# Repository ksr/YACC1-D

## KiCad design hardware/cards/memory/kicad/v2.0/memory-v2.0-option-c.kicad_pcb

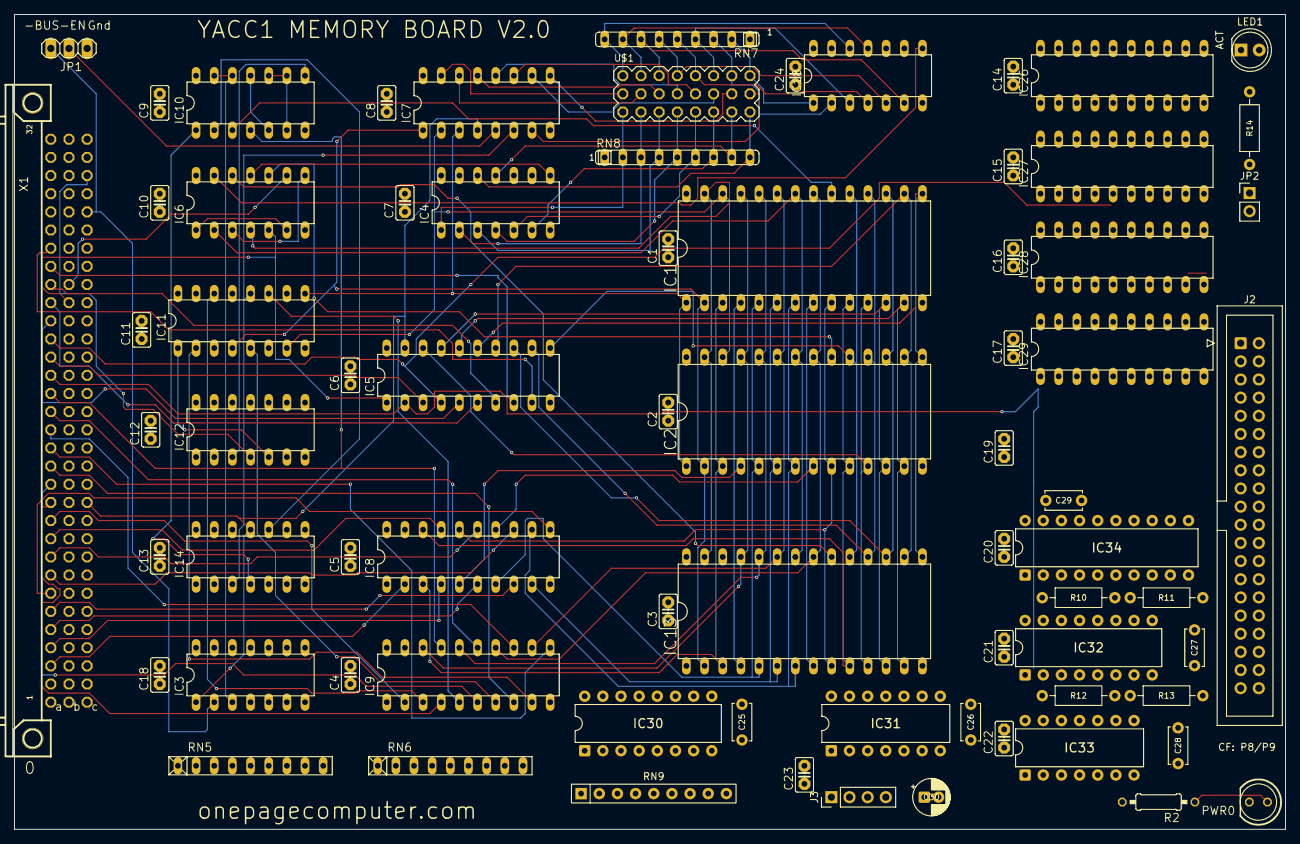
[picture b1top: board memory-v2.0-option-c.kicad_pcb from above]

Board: 4 copper layers, 177.8 x 114.0 mm, 73 parts (0 on the bottom side), 147 nets.

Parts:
C1, C2, C3, C4, C5, C6, C7, C8, C9, C10, C11, C12, C13, C14, C15, C16, C17, C18, C19, C20, C21, C22, C23, C24: C025-025X050
C25, C26, C27, C28, C29: 100n; C_Disc_D5.0mm_W2.5mm_P5.00mm
C30: 10u; CP_Radial_D5.0mm_P2.00mm
IC1, IC2, IC13: DIL28-6
IC3: 74LS32N; DIL14
IC4, IC18: 74ALS30N; DIL14
IC5: 74LS245N; DIL20
IC6, IC14: 74LS04N; DIL14
IC7: 74LS138N; DIL16
IC8, IC9: 74LS244N; DIL20
IC10: 74ALS00N; DIL14
IC11: 74LS157N; DIL16
IC12: 74LS74N; DIL14
IC26, IC27, IC28, IC29: 74LS374N; DIL20
IC30: 74LS138; DIP-16_W7.62mm
IC31: 74LS32; DIP-14_W7.62mm
IC32: 74LS175; DIP-16_W7.62mm
IC33: 74LS08; DIP-14_W7.62mm
IC34: 74LS245; DIP-20_W7.62mm
J2: IDE 40; IDC-Header_2x20_P2.54mm_Vertical
J3: POWER; PinHeader_1x04_P2.54mm_Vertical
JP1: 1X03
JP2: PIN20 5V; PinHeader_1x02_P2.54mm_Vertical
LED1: ACT yellow; LED_D5.0mm
PWR0: LED5MM
R2: 330; 0207_10
R10, R11, R12, R13: 10k; R_Axial_DIN0207_L6.3mm_D2.5mm_P10.16mm_Horizontal
R14: 1k; R_Axial_DIN0207_L6.3mm_D2.5mm_P10.16mm_Horizontal
RN5, RN6: RN-9
RN7, RN8: SIL9
RN9: 10k x8; R_Array_SIP9
U$1: PIN_3X8
X1: FABC96R

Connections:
-BUS-EN: IC3.2, JP1.1, X1.C28
-HI-RAM: IC2.20, IC6.10
-IO-RD: IC31.5, X1.B25
-IO-WR: IC31.2, IC31.10, X1.B26
-MEM-RD: IC5.1, IC6.5, X1.B23
-MEM-WR: IC6.9, X1.B24
-RESET: IC12.4, IC32.1, IC33.4, X1.C30
-ROM-CS: IC6.12, IC13.20
-TMP-REG-LD0: IC14.1, X1.B28
-TMP-REG-LD1: IC14.13, X1.B30
-TMP-REG-RD0: IC26.1, IC27.1, X1.B27
-TMP-REG-RD1: IC28.1, IC29.1, X1.B29
-VMA: IC3.1, IC5.19, IC7.4, IC14.11, X1.C12
/Sheet 3/-LO-RAM: IC1.20, IC10.3
/Sheet 7/-CFOE: IC33.3, IC33.9, IC33.10, IC34.19
/Sheet 7/-CFRESET: IC33.6, J2.1
/Sheet 7/-DASP: J2.39, R12.2
/Sheet 7/-DMACK: J2.29, R13.2
/Sheet 7/-IOR: IC31.6, IC33.1, IC34.1, J2.25
/Sheet 7/-IOW: IC31.8, IC33.2, J2.23
/Sheet 7/-P8SEL: IC30.15, IC31.1
/Sheet 7/-P9SEL: IC30.14, IC31.4, IC31.9
/Sheet 7/-PDIAG: J2.34, R11.2
/Sheet 7/-SRST: IC32.14, IC33.5
/Sheet 7/ACTK: IC33.8, LED1.1
/Sheet 7/CFD0: IC34.18, J2.17, RN9.2
/Sheet 7/CFD1: IC34.17, J2.15, RN9.3
/Sheet 7/CFD2: IC34.16, J2.13, RN9.4
/Sheet 7/CFD3: IC34.15, J2.11, RN9.5
/Sheet 7/CFD4: IC34.14, J2.9, RN9.6
/Sheet 7/CFD5: IC34.13, J2.7, RN9.7
/Sheet 7/CFD6: IC34.12, J2.5, RN9.8
/Sheet 7/CFD7: IC34.11, J2.3, RN9.9
/Sheet 7/DA0: IC32.2, J2.35
/Sheet 7/DA1: IC32.7, J2.33
/Sheet 7/DA2: IC32.10, J2.36
/Sheet 7/IORDY: J2.27, R10.2
/Sheet 7/LATCHCLK: IC31.3, IC32.9
/Sheet 7/LEDA2: LED1.2, R14.2
/Sheet 7/PIN20: J2.20, JP2.2
ADDR0: IC8.2, X1.A3
ADDR1: IC8.4, X1.A4
ADDR2: IC8.6, X1.A5
ADDR3: IC8.8, X1.A6
ADDR4: IC8.11, X1.A7
ADDR5: IC8.13, X1.A8
ADDR6: IC8.15, X1.A9
ADDR7: IC8.17, X1.A10
ADDR8: IC9.2, X1.A11
ADDR9: IC9.4, X1.A12
ADDR10: IC9.6, X1.A13
ADDR11: IC9.8, X1.A14
ADDR12: IC9.11, X1.A15
ADDR13: IC9.13, X1.A16
ADDR14: IC9.15, X1.A17
ADDR15: IC9.17, IC10.4, X1.A18
BADDR0: IC1.10, IC2.10, IC8.18, IC13.10
BADDR1: IC1.9, IC2.9, IC8.16, IC13.9
BADDR2: IC1.8, IC2.8, IC8.14, IC13.8
BADDR3: IC1.7, IC2.7, IC8.12, IC13.7
BADDR4: IC1.6, IC2.6, IC8.9, IC13.6
BADDR5: IC1.5, IC2.5, IC8.7, IC13.5
BADDR6: IC1.4, IC2.4, IC8.5, IC13.4
BADDR7: IC1.3, IC2.3, IC8.3, IC13.3
BADDR8: IC1.25, IC2.25, IC9.18, IC13.25
BADDR9: IC1.24, IC2.24, IC9.16, IC13.24
BADDR10: IC1.21, IC2.21, IC9.14, IC13.21
BADDR11: IC1.23, IC2.23, IC9.12, IC13.23
BADDR12: IC1.2, IC2.2, IC7.1, IC11.4, IC13.2
BADDR13: IC1.26, IC2.26, IC7.2, IC11.7
BADDR14: IC1.1, IC2.1, IC7.3, IC11.9
BADDR15: IC7.6, IC11.12, IC14.3
BDATA0: IC1.11, IC2.11, IC5.18, IC13.11
BDATA1: IC1.12, IC2.12, IC5.17, IC13.12
BDATA2: IC1.13, IC2.13, IC5.16, IC13.13
BDATA3: IC1.15, IC2.15, IC5.15, IC13.15
BDATA4: IC1.16, IC2.16, IC5.14, IC13.16
BDATA5: IC1.17, IC2.17, IC5.13, IC13.17
BDATA6: IC1.18, IC2.18, IC5.12, IC13.18
BDATA7: IC1.19, IC2.19, IC5.11, IC13.19
DATA0: IC5.2, IC26.2, IC26.3, IC28.2, IC28.3, IC32.4, IC34.2, RN5.2, X1.A19
DATA1: IC5.3, IC26.4, IC26.5, IC28.4, IC28.5, IC32.5, IC34.3, RN5.3, X1.A20
DATA2: IC5.4, IC26.6, IC26.7, IC28.6, IC28.7, IC32.12, IC34.4, RN5.4, X1.A21
DATA3: IC5.5, IC26.8, IC26.9, IC28.8, IC28.9, IC32.13, IC34.5, RN5.5, X1.A22
DATA4: IC5.6, IC26.12, IC26.13, IC28.12, IC28.13, IC34.6, RN5.6, X1.A23
DATA5: IC5.7, IC26.14, IC26.15, IC28.14, IC28.15, IC34.7, RN5.7, X1.A24
DATA6: IC5.8, IC26.16, IC26.17, IC28.16, IC28.17, IC34.8, RN5.8, X1.A25
DATA7: IC5.9, IC26.18, IC26.19, IC28.18, IC28.19, IC34.9, RN5.9, X1.A26
DATA8: IC27.2, IC27.3, IC29.2, IC29.3, RN6.2, X1.A27
DATA9: IC27.4, IC27.5, IC29.4, IC29.5, RN6.3, X1.A28
DATA10: IC27.6, IC27.7, IC29.6, IC29.7, RN6.4, X1.A29
DATA11: IC27.8, IC27.9, IC29.8, IC29.9, RN6.5, X1.A30
DATA12: IC27.12, IC27.13, IC29.12, IC29.13, RN6.6, X1.B3
DATA13: IC27.14, IC27.15, IC29.14, IC29.15, RN6.7, X1.B4
DATA14: IC27.16, IC27.17, IC29.16, IC29.17, RN6.8, X1.B5
DATA15: IC27.18, IC27.19, IC29.18, IC29.19, RN6.9, X1.B6
FORCE-ROM: IC11.1, IC12.5
GND: C1.2, C2.2, C3.2, C4.2, C5.2, C6.2, C7.2, C8.2, C9.2, C10.2, C11.2, C12.2, C13.2, C14.2, C15.2, C16.2, C17.2, C18.2, C19.1, C20.1, C21.1, C22.1, C23.1, C24.1, C25.2, C26.2, C27.2, C28.2, C29.2, C30.2, IC1.14, IC2.14, IC3.4, IC3.5, IC3.7, IC3.9, IC3.10, IC3.12, IC3.13, IC4.7, IC5.10, IC6.7, IC7.8, IC8.1, IC8.10, IC8.19, IC9.1, IC9.10, IC9.19, IC10.7, IC11.8, IC11.15, IC12.2, IC12.7, IC12.10, IC12.11, IC12.12, IC12.13, IC13.14, IC14.7, IC18.7, IC26.10, IC27.10, IC28.10, IC29.10, IC30.4, IC30.5, IC30.8, IC31.7, IC31.12, IC31.13, IC32.8, IC33.7, IC33.12, IC33.13, IC34.10, J2.2, J2.19, J2.22, J2.24, J2.26, J2.28, J2.30, J2.37, J2.40, J3.2, J3.3, JP1.3, PWR0.K, RN5.1, RN6.1, X1.A1, X1.A32, X1.B1, X1.B32, X1.C1, X1.C32
IO-ADDR0: IC30.1, X1.C7
IO-ADDR1: IC30.2, X1.C8
IO-ADDR2: IC30.3, X1.C9
IO-ADDR3: IC30.6, X1.C10
unnamed: IC1.22, IC2.22, IC6.2, IC13.22
unnamed: IC1.27, IC2.27, IC6.4, IC13.27
unnamed: IC4.1, RN8.2, U$1.17
unnamed: IC4.2, RN8.3, U$1.18
unnamed: IC4.3, RN8.4, U$1.19
unnamed: IC4.4, RN8.5, U$1.20
unnamed: IC4.5, RN8.6, U$1.21
unnamed: IC4.6, RN8.7, U$1.22
unnamed: IC4.11, RN8.8, U$1.23
unnamed: IC4.12, RN8.9, U$1.24
unnamed: IC4.8, IC6.11
unnamed: IC6.1, IC6.6
unnamed: IC6.3, IC6.8
unnamed: IC7.5, JP1.2
unnamed: IC7.15, U$1.9
unnamed: IC7.14, U$1.10
unnamed: IC7.13, U$1.11
unnamed: IC7.12, U$1.12
unnamed: IC7.11, U$1.13
unnamed: IC7.10, U$1.14
unnamed: IC7.9, U$1.15
unnamed: IC7.7, U$1.16
unnamed: IC10.1, IC14.4
unnamed: IC10.2, IC14.10
unnamed: IC10.5, IC10.11
unnamed: IC10.6, IC10.9, IC10.10
unnamed: IC10.8, IC12.3
unnamed: IC3.3, IC10.12, IC10.13
unnamed: IC9.9, IC11.2
unnamed: IC9.7, IC11.5
unnamed: IC9.5, IC11.11
unnamed: IC9.3, IC11.14
unnamed: IC14.2, IC26.11, IC27.11
unnamed: IC14.12, IC28.11, IC29.11
unnamed: IC18.1, RN7.2, U$1.8
unnamed: IC18.2, RN7.3, U$1.7
unnamed: IC18.3, RN7.4, U$1.6
unnamed: IC18.4, RN7.5, U$1.5
unnamed: IC18.5, RN7.6, U$1.4
unnamed: IC18.6, RN7.7, U$1.3
unnamed: IC18.11, RN7.8, U$1.2
unnamed: IC18.12, RN7.9, U$1.1
unnamed: IC6.13, IC18.8
unnamed: PWR0.A, R2.1
VCC: C1.1, C2.1, C3.1, C4.1, C5.1, C6.1, C7.1, C8.1, C9.1, C10.1, C11.1, C12.1, C13.1, C14.1, C15.1, C16.1, C17.1, C18.1, C19.2, C20.2, C21.2, C22.2, C23.2, C24.2, C25.1, C26.1, C27.1, C28.1, C29.1, C30.1, IC1.28, IC2.28, IC3.14, IC4.14, IC5.20, IC6.14, IC7.16, IC8.20, IC9.20, IC10.14, IC11.3, IC11.6, IC11.10, IC11.13, IC11.16, IC12.1, IC12.14, IC13.28, IC14.14, IC18.14, IC26.20, IC27.20, IC28.20, IC29.20, IC30.16, IC31.14, IC32.16, IC33.14, IC34.20, J2.38, J3.1, JP2.1, R2.2, R10.1, R11.1, R12.1, R13.1, R14.1, RN7.1, RN8.1, RN9.1, X1.A2, X1.A31, X1.B2, X1.B31, X1.C2, X1.C31
